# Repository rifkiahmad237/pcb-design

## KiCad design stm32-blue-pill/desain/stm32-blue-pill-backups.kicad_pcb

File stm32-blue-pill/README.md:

# Dokumentasi Desain PCB STM32F103C8T6

## 1. Kapasitor Decoupling

### **Mengapa Diperlukan?**
- Menstabilkan tegangan suplai (**VDD**) agar tidak berfluktuasi akibat switching internal IC.
- Mengurangi noise frekuensi tinggi yang dapat mengganggu operasi mikrokontroler.
- Menyediakan arus instan saat mikrokontroler mengalami perubahan keadaan logika secara cepat.

### **Penempatan Kapasitor Decoupling**
- Harus **sedekat mungkin** dengan pin daya IC untuk mengurangi efek induktansi jalur PCB.
- Nilai umum yang digunakan:
  - **100nF (0.1µF)** untuk setiap pin **VDD**.
  - **4.7µF – 10µF** elektrolit/tantalum untuk stabilisasi tambahan.
  - Untuk filter noise frekuensi tinggi, bisa ditambahkan **1nF**.

---

## 2. Perbedaan Rangkaian Filter VDD dan VDDA

| Tegangan | Fungsi | Rangkaian Filter |
|----------|--------|-----------------|
| **VDD** | Daya utama inti mikrokontroler dan periferal digital. | Kapasitor **100nF + 4.7µF** untuk stabilisasi tegangan. |
| **VDDA** | Daya untuk bagian analog (ADC, DAC). | Filter **RC atau LC** untuk meredam noise dari VDD. |

- **VDDA lebih sensitif terhadap noise**, sehingga perlu pemfilteran tambahan menggunakan ferrite bead atau resistor.

---

## 3. Filter Ferrite Bead untuk VDDA

### **Mengapa Perlu Filter?**
- Noise dari **switching digital** di VDD bisa mempengaruhi ADC jika langsung masuk ke VDDA.
- Ferrite bead berfungsi sebagai **low-pass filter**, menghilangkan noise frekuensi tinggi.
- Rekomendasi umum:
  - **Ferrite bead 600Ω @ 100MHz** (contoh: Murata BLM18AG601SN1D).
  - **Kapasitor 100nF + 1µF** setelah ferrite bead.

### **Alternatif: Filter RC**
- Jika ferrite bead tidak tersedia, bisa menggunakan **resistor 10Ω + kapasitor 1µF** sebagai pengganti.
- Namun, penggunaan resistor bisa menyebabkan sedikit **drop tegangan pada VDDA**.

---

## 4. Sumber Noise Frekuensi Tinggi

| Sumber Noise | Penyebab | Efek pada PCB |
|-------------|---------|--------------|
| **Switching internal mikrokontroler** | Perubahan logika cepat dalam CPU & GPIO | Lonjakan arus sesaat, fluktuasi tegangan pada VDD. |
| **Regulator Switching (DC-DC Converter)** | Frekuensi switching tinggi (150kHz–1MHz) | Ripple tegangan yang bisa masuk ke VDD/VDDA. |
| **Clock dan Kristal Osilator** | Sinyal clock eksternal (8MHz, 16MHz, dll.) | Noise EMI pada jalur PCB. |
| **Desain PCB yang buruk** | Jalur suplai daya terlalu panjang, ground plane tidak optimal | Ground bounce, crosstalk antar sinyal. |
| **Periferal eksternal (motor, relay, LCD)** | Arus transien tinggi | Gangguan pada ADC, kemungkinan reset mendadak. |

### **Solusi untuk Mengurangi Noise:**
- **Gunakan kapasitor decoupling dengan benar**.
- **Gunakan ferrite bead pada VDDA untuk menghilangkan noise dari VDD**.
- **Pastikan tata letak PCB optimal dengan ground plane yang baik**.
- **Pisahkan jalur daya analog dan digital** jika memungkinkan.

---

## 5. VDDA dan VDD: Mengapa Filter Tetap Menghubungkan Ke 3.3V?

- **VDDA** dan **VDD** menggunakan sumber **3.3V yang sama**, namun **VDDA lebih sensitif terhadap noise** dari bagian digital (VDD).
- **Low-pass filter** menggunakan **ferrite bead** dan **kapasitor** bertujuan untuk **mengurangi noise frekuensi tinggi** pada **VDDA** tanpa memisahkan sumber daya sepenuhnya.
- Memisahkan sumber daya untuk VDDA dan VDD bisa dilakukan dengan menggunakan **regulator terpisah**, namun umumnya cukup dengan menggunakan filter untuk penyaringan noise.

---

## 6. Perhitungan Kapasitor untuk Crystal Oscillator (16 MHz)

### **Langkah-langkah Menghitung Kapasitor**

1. **Tentukan Nilai Kapasitansi Seri dan Parasitik dari Kristal**
   - Nilai **C_L** untuk kristal dapat ditemukan di datasheet kristal tersebut (biasanya dalam kisaran 12 pF hingga 30 pF untuk kristal 16 MHz).
   - **Kapasitansi parasitik** PCB biasanya sekitar 2 pF hingga 5 pF.

2. **Rumus Perhitungan Kapasitor Eksternal**
   - Untuk menghitung nilai kapasitor eksternal (C1 dan C2) yang digunakan di sisi kristal, gunakan rumus berikut:
   
   \[
   C_1 = C_2 = 2 \times C_L - C_{parasitik}
   \]

   Di mana:
   - **C_L** adalah kapasitan yang dibutuhkan oleh kristal (misalnya 18 pF),
   - **C_{parasitik}** adalah kapasitansi parasitik (misalnya 5 pF),
   - **C_1** dan **C_2** adalah kapasitor yang dibutuhkan.

### **Contoh Perhitungan**
Misalnya, untuk kristal 16 MHz dengan **C_L = 18 pF** dan **kapasitansi parasitik PCB = 5 pF**:

\[
C_1 = C_2 = 2 \times 18\,\text{pF} - 5\,\text{pF} = 36\,\text{pF} - 5\,\text{pF} = 31\,\text{pF}
\]

Jadi, nilai kapasitor yang digunakan adalah **31 pF** untuk C1 dan C2.

---

## 7. USB (Micro USB) Pinout

Pada desain STM32F103C8T6 yang hanya berfungsi sebagai **peripheral device** (bukan host USB), pin **Shield** dan **Pin ID** dapat **dibiarkan mengambang** atau **floating**.

### **Pin Shield**
- **Fungsi**: Pin ini digunakan untuk **grounding** dan **pelindung** terhadap interferensi elektromagnetik (EMI).
- **Koneksi pada perangkat STM32**: Pin **Shield** dapat **dibiarkan mengambang** atau tidak terhubung langsung ke ground jika perangkat hanya berfungsi sebagai **peripheral device**. Tidak perlu menghubungkannya ke ground.

### **Pin ID**
- **Fungsi**: Pin ini digunakan untuk menentukan apakah perangkat bertindak sebagai **host** atau **peripheral** dalam mode **USB OTG**.
- **Koneksi pada perangkat STM32**: Jika STM32 hanya bertindak sebagai **peripheral device**, pin **ID** dapat **dibiarkan mengambang** atau **floating**. Tidak perlu dihubungkan ke ground karena perangkat tidak akan berfungsi sebagai host USB.

Jadi, pada desain STM32 yang berfungsi sebagai **device-only**, baik pin **Shield** maupun **Pin ID** dapat dibiarkan **floating** tanpa mengganggu fungsionalitas perangkat.

Pada desain USB untuk STM32F103C8T6 yang berfungsi sebagai **peripheral device**, resistor **pull-up 1.5kΩ** perlu ditambahkan pada **pin D+** untuk memungkinkan perangkat dikenali oleh host USB.

### **Fungsi Resistor Pull-up**
- Resistor **1.5kΩ** dihubungkan antara **pin D+** dan **VBUS** (5V) untuk memberi sinyal ke host bahwa perangkat ini adalah **peripheral**.
- Pin **D-** tidak memerlukan resistor pull-up, hanya **D+** yang membutuhkan.
- Dengan resistor ini, perangkat USB dapat berkomunikasi dengan host seperti komputer atau perangkat lainnya.

### **Koneksi**
- **Pin D+** dihubungkan ke **VBUS** melalui resistor **1.5kΩ**.

### **Catatan**
- Penambahan resistor pull-up 1.5kΩ pada pin D+ ini **tidak berlaku untuk semua mikrokontroler STM32**. Namun, pada **STM32F103C8T6**, resistor ini sangat diperlukan agar perangkat dapat dikenali dan berfungsi sebagai peripheral USB.

## 8. Pull-up Resistor pada I2C

Pada komunikasi **I2C**, resistor **pull-up** diperlukan pada jalur **SDA (Serial Data)** dan **SCL (Serial Clock)** karena protokol I2C menggunakan **open-drain**. Tanpa resistor ini, jalur komunikasi bisa **floating**, yang menyebabkan kesalahan dalam transmisi data.

### **Fungsi Pull-up Resistor**
1. **Menjaga Level Logika "High"**  
   - Perangkat I2C hanya dapat menarik jalur ke LOW (GND) tetapi tidak bisa secara aktif mendorongnya ke HIGH.  
   - Resistor pull-up memastikan bahwa saat tidak ada perangkat yang menarik ke LOW, **SDA dan SCL tetap berada di level HIGH**.

2. **Menentukan Kecepatan Transisi Sinyal**  
   - Resistor pull-up mempengaruhi seberapa cepat sinyal berubah dari LOW ke HIGH.
   - Untuk **I2C Fast Mode (400kHz)**, biasanya digunakan **resistor 2.2kΩ** untuk memastikan transisi yang cepat.

3. **Mencegah Floating Signal & Error**  
   - Tanpa pull-up resistor, jalur **SDA** dan **SCL** bisa berada dalam kondisi tidak stabil (floating), menyebabkan komunikasi I2C gagal atau error.

### **Nilai Pull-up Resistor Berdasarkan Kecepatan I2C**
| Kecepatan I2C | Nilai Resistor Pull-up |
|--------------|----------------------|
| **100 kHz (Standard Mode)** | **4.7kΩ – 10kΩ** |
| **400 kHz (Fast Mode)** | **1.8kΩ – 4.7kΩ** (umumnya **2.2kΩ**) |
| **1 MHz (Fast Mode Plus)** | **1kΩ – 2.2kΩ** |
| **3.4 MHz (High-Speed Mode)** | **200Ω – 1kΩ** |

### **Cara Menghubungkan Pull-up Resistor**
- **SDA → Resistor 2.2kΩ → VCC (3.3V atau 5V, sesuai tegangan I2C)**  
- **SCL → Resistor 2.2kΩ → VCC (3.3V atau 5V, sesuai tegangan I2C)**  

*(Pastikan nilai VCC sesuai dengan level tegangan yang digunakan oleh perangkat I2C! Jika STM32 menggunakan 3.3V, maka pull-up harus ke 3.3V.)*

### **Kesimpulan**
- **Pull-up resistor sangat penting dalam komunikasi I2C** untuk menjaga kestabilan sinyal.  
- Nilai **2.2kΩ** digunakan untuk **I2C Fast Mode (400kHz)** agar transisi sinyal cepat dan stabil.  
- Tanpa resistor pull-up, **SDA dan SCL bisa floating**, menyebabkan error atau komunikasi yang tidak berjalan.  

## 9. Pemilihan Footprint Komponen

Memilih footprint yang tepat sangat penting agar komponen dapat dipasang dengan baik dan proses soldering berjalan lancar. Berikut adalah panduan dalam memilih footprint yang sesuai.

### **1. Jenis Footprint Berdasarkan Komponen**
Komponen PCB memiliki dua jenis utama berdasarkan cara pemasangannya:
- **Through-Hole (THT)** → Memiliki lubang pada PCB untuk kaki komponen. Cocok untuk solder manual.
- **Surface Mount Device (SMD)** → Tidak memiliki lubang, hanya pad tembaga. Cocok untuk reflow soldering.

Contoh package dan footprint yang sering digunakan:
| **Komponen** | **Jenis Package** | **Footprint PCB** |
|-------------|-----------------|------------------|
| **STM32F103C8T6** | LQFP-48 | LQFP-48 (7x7mm, 0.5mm pitch) |
| **Resistor SMD** | 0805 | 0805 (2.0mm x 1.25mm) |
| **Kapasitor SMD** | 0603 | 0603 (1.6mm x 0.8mm) |
| **LED SMD** | 1206 | 1206 (3.2mm x 1.6mm) |
| **Konektor USB Micro** | SMD/THT | USB-Micro-B-5P |
| **Crystal 16MHz** | HC-49S | HC-49S (Through-hole) atau SMD-3225 |
| **AMS1117-3.3V** | SOT-223 | SOT-223 (SMD) |

### **2. Faktor yang Harus Diperhatikan dalam Memilih Footprint**
1. **Sesuai dengan Datasheet Komponen**  
   - Periksa dimensi kaki, pitch (jarak antar pin), dan ukuran pad solder.  
2. **Ukuran Pad dan Lubang Solder**  
   - **THT** → Lubang harus sedikit lebih besar dari kaki komponen agar mudah dipasang.  
   - **SMD** → Pad harus cukup besar untuk soldering manual atau reflow.  
3. **Clearance Antar Komponen**  
   - Pastikan ada ruang cukup agar soldering tidak sulit.  
   - Untuk sinyal high-speed, gunakan **clearance minimal 0.2mm – 0.5mm**.  
4. **Metode Soldering**  
   - **Manual** → Gunakan footprint yang lebih besar agar lebih mudah disolder.  
   - **Reflow** → Gunakan footprint standar sesuai datasheet.  
5. **Orientasi & Polaritas Komponen**  
   - Pin 1 pada IC harus sesuai dengan marking di footprint PCB.  
   - LED, kapasitor elektrolit, dan dioda harus memiliki tanda polaritas.  

### **3. Cara Memeriksa Footprint Sebelum Produksi**
- Gunakan **3D Viewer di software PCB** (seperti KiCad atau Altium) untuk mengecek dimensi.  
- Cetak layout PCB dalam skala **1:1**, lalu tempelkan komponen fisik untuk memastikan kecocokan.  
- Periksa **clearance antar komponen** terutama pada area padat seperti konektor dan IC.  
- Pastikan **solder pad cukup besar** agar mudah disolder.  
### **4. Jenis-Jenis Package Komponen dan Penggunaannya**

| **Jenis Package** | **Deskripsi** | **Digunakan untuk** | **Gambar** |
|------------------|--------------|----------------------|------------|
| **SOIC (Small Outline IC)** | IC dengan kaki menonjol keluar di kedua sisi, lebih besar dari TSSOP. | IC dengan jumlah pin sedang, seperti op-amp atau mikrokontroler kecil. | *(Tambahkan gambar di sini)* |
| **TSSOP (Thin Shrink Small Outline Package)** | Versi lebih tipis dan rapat dari SOIC, menghemat ruang PCB. | IC kecil dengan banyak pin seperti regulator atau sensor. | *(Tambahkan gambar di sini)* |
| **QFP (Quad Flat Package)** | IC dengan kaki di keempat sisi, tersedia dalam berbagai ukuran. | STM32F103C8T6 (LQFP-48), mikrokontroler, FPGA. | *(Tambahkan gambar di sini)* |
| **QFN (Quad Flat No-Lead)** | IC tanpa kaki menonjol, hanya pad solder di bawahnya. | IC kecil dengan performa tinggi, konverter daya, sensor digital. | *(Tambahkan gambar di sini)* |
| **BGA (Ball Grid Array)** | IC dengan bola solder di bawahnya, membutuhkan reflow soldering. | Prosesor, memori flash, IC berkecepatan tinggi. | *(Tambahkan gambar di sini)* |
| **0805 (SMD Resistor/Kapasitor)** | 2.0mm x 1.25mm, mudah disolder secara manual. | Resistor dan kapasitor SMD umum. | *(Tambahkan gambar di sini)* |
| **0603 (SMD Resistor/Kapasitor)** | 1.6mm x 0.8mm, lebih kecil dari 0805. | Resistor dan kapasitor untuk desain yang lebih ringkas. | *(Tambahkan gambar di sini)* |
| **0402 (SMD Resistor/Kapasitor)** | 1.0mm x 0.5mm, sulit disolder manual. | Desain berukuran kecil dengan kepadatan tinggi. | *(Tambahkan gambar di sini)* |

💡 **Catatan**:  
- **QFP lebih mudah disolder manual dibanding QFN dan BGA** karena memiliki kaki yang terlihat.  
- **QFN dan BGA membutuhkan soldering reflow dan sulit diperbaiki secara manual**.  
- **Komponen ukuran 0805 lebih mudah disolder dibanding 0603 atau 0402**, sehingga lebih cocok untuk pemula.  

🔹 Untuk menambahkan gambar, bisa menggunakan format markdown berikut setelah mengunggah gambarnya:  
### **Kesimpulan**
- Gunakan **footprint yang sesuai datasheet** untuk menghindari kesalahan produksi.  
- Perhatikan **ukuran pad, lubang solder, dan clearance** agar proses soldering lebih mudah.  
- Lakukan pengecekan dengan **3D viewer atau cetak layout skala 1:1** sebelum memesan PCB.  
- Pastikan **IC, konektor, dan komponen dengan polaritas** memiliki marking yang jelas agar tidak salah pasang.  

# Faktor yang Mempengaruhi Kualitas Jalur pada PCB  

Desain jalur pada PCB sangat berpengaruh terhadap kualitas sinyal, terutama pada sinyal frekuensi tinggi. Berikut adalah faktor-faktor utama yang mempengaruhi kualitas jalur:  

## 1. Impedansi Jalur  

### **Apa itu Impedansi?**  
Impedansi (\(Z\)) adalah hambatan total dalam jalur PCB yang terdiri dari resistansi, induktansi, dan kapasitansi. Nilai impedansi sangat penting dalam desain **high-speed signal** dan **differential pairs**.  

### **Faktor yang Mempengaruhi Impedansi:**  
| Faktor | Pengaruh terhadap Impedansi |
|--------|-----------------------------|
| **Lebar jalur** | Jalur lebih lebar → Impedansi lebih rendah |
| **Jarak ke ground plane** | Jarak lebih dekat → Impedansi lebih rendah |
| **Konstanta dielektrik PCB (\( \varepsilon_r \))** | \( \varepsilon_r \) lebih tinggi → Impedansi lebih rendah |
| **Ketebalan tembaga** | Tembaga lebih tebal → Impedansi lebih rendah |
| **Jarak antar pasangan diferensial** | Jarak lebih dekat → Impedansi lebih rendah |

### **Dampak jika impedansi tidak sesuai:**  
- **Refleksi sinyal**, yang menyebabkan distorsi data.  
- **Penurunan kecepatan komunikasi** akibat sinyal yang tidak terdeteksi dengan baik.  
- **Ketidaksesuaian dengan standar (USB, HDMI, PCIe, dll.)**.  

---

## 2. Induktansi Jalur  

### **Apa itu Induktansi?**  
Induktansi adalah kemampuan jalur PCB untuk menyimpan energi dalam bentuk medan magnet ketika arus melewatinya.  

### **Faktor yang Meningkatkan Induktansi:**  
| Faktor | Pengaruh terhadap Induktansi |
|--------|-----------------------------|
| **Jalur lebih panjang** | Induktansi lebih tinggi |
| **Jalur lebih sempit** | Induktansi lebih tinggi |
| **Jarak lebih jauh dari ground plane** | Induktansi lebih tinggi |
| **Tidak adanya ground return path yang dekat** | Induktansi lebih tinggi |

### **Dampak Induktansi Tinggi:**  
- **Menurunkan integritas sinyal** akibat distorsi dan ringing.  
- **Menyebabkan overshoot dan undershoot pada sinyal digital**.  
- **Menimbulkan EMI (Electromagnetic Interference) yang lebih besar**.  

✅ **Solusi:**  
- Gunakan **ground plane** yang dekat dengan jalur.  
- Jaga agar jalur tetap **pendek dan lebar**.  
- Untuk sinyal high-speed, gunakan **jalur diferensial** untuk mengurangi EMI.  

---

## 3. Kapasitansi Jalur  

### **Apa itu Kapasitansi?**  
Kapasitansi adalah kemampuan jalur untuk menyimpan muatan listrik dalam medan listrik antara jalur dan ground plane.  

### **Faktor yang Meningkatkan Kapasitansi:**  
| Faktor | Pengaruh terhadap Kapasitansi |
|--------|-----------------------------|
| **Jarak kecil antara jalur dan ground plane** | Kapasitansi lebih besar |
| **Jalur lebih lebar di dekat ground plane** | Kapasitansi lebih besar |
| **Material PCB dengan konstanta dielektrik tinggi (\( \varepsilon_r \))** | Kapasitansi lebih besar |

### **Dampak Kapasitansi Tinggi:**  
- **Sinyal menjadi lebih lambat** karena waktu propagasi meningkat.  
- **Pelemahan sinyal (signal attenuation)**, terutama pada frekuensi tinggi.  
- **Cross-talk antar jalur meningkat**, menyebabkan interferensi antar sinyal.  

✅ **Solusi:**  
- Jaga jarak antara jalur dan ground plane sesuai perhitungan impedansi.  
- Gunakan **material dengan konstanta dielektrik rendah** untuk mengurangi efek kapasitif.  
- Gunakan jalur **lebih sempit** untuk mengurangi luas permukaan yang bersentuhan dengan ground plane.  

---

## 4. Resistansi Jalur  

### **Apa itu Resistansi?**  
Resistansi adalah hambatan listrik yang terjadi akibat sifat material tembaga dan panjang jalur pada PCB.  

### **Faktor yang Meningkatkan Resistansi:**  
| Faktor | Pengaruh terhadap Resistansi |
|--------|-----------------------------|
| **Jalur lebih panjang** | Resistansi lebih tinggi |
| **Jalur lebih sempit** | Resistansi lebih tinggi |
| **Ketebalan tembaga lebih tipis** | Resistansi lebih tinggi |

### **Dampak Resistansi Tinggi:**  
- **Tegangan drop lebih besar**, terutama pada jalur daya.  
- **Panas berlebih pada PCB**, yang dapat menyebabkan degradasi komponen.  
- **Penurunan performa sinyal**, terutama pada frekuensi tinggi.  

✅ **Solusi:**  
- Gunakan **jalur lebih lebar** untuk daya tinggi.  
- Gunakan **tembaga lebih tebal** (misalnya 2 oz/ft² dibandingkan 1 oz/ft²).  
- Minimalkan panjang jalur untuk mengurangi resistansi total.  

---

## 5. Kesimpulan  

Untuk mendesain PCB dengan kualitas sinyal yang baik, pertimbangkan faktor-faktor berikut:  

| Faktor | Efek Positif | Efek Negatif |
|--------|-------------|-------------|
| **Impedansi yang sesuai** | Mengurangi refleksi, kompatibel dengan standar komunikasi | Jika salah, sinyal bisa terdistorsi |
| **Induktansi rendah** | Mengurangi EMI dan ringing | Jika tinggi, menyebabkan gangguan sinyal |
| **Kapasitansi terkontrol** | Mempertahankan kecepatan sinyal | Jika tinggi, bisa memperlambat sinyal dan menyebabkan cross-talk |
| **Resistansi rendah** | Mengurangi panas dan tegangan drop | Jika tinggi, menyebabkan penurunan performa dan overheat |

**Rekomendasi umum untuk jalur PCB:**  
- Gunakan **impedansi terkendali** untuk sinyal high-speed.  
- Pastikan **ground plane selalu dekat dengan jalur** untuk mengurangi EMI dan meningkatkan return path.  
- Gunakan **jalur lebar untuk daya**, dan **jalur sempit dengan perhitungan yang sesuai untuk sinyal high-speed**.  
- Pilih material PCB yang sesuai untuk kebutuhan desain (misalnya FR4 atau Rogers untuk RF).  

Dengan memahami konsep ini, desain PCB akan lebih optimal dalam performa, daya tahan, dan kualitas sinyal. 🚀  

# Differential Pair pada Desain PCB (USB)

Pada desain PCB dengan sinyal **differential pair** seperti USB, penting untuk mengatur beberapa parameter untuk menjaga kualitas sinyal dan memastikan impedansi sesuai standar.

## 1. **Width (Lebar Jalur)**
- **Width** adalah lebar dari jalur **differential pair** (misalnya D+ dan D- untuk USB).
- Lebar jalur berpengaruh pada **impedansi** sinyal.
- Untuk USB, impedansi yang diinginkan adalah sekitar **90Ω**.
- Lebar jalur yang lebih lebar akan menghasilkan **impedansi lebih rendah**, sementara jalur yang lebih sempit menghasilkan **impedansi lebih tinggi**.
- Lebar jalur harus disesuaikan dengan **ketebalan tembaga** pada PCB dan **konstanta dielektrik** bahan PCB.

## 2. **Gap (Jarak Antar Jalur)**
- **Gap** adalah jarak antara dua jalur yang membentuk differential pair (D+ dan D-).
- Jarak yang tepat antara jalur ini penting untuk menjaga **impedansi**.
- Jika gap terlalu kecil, impedansi bisa terlalu rendah, menyebabkan **refleksi** dan **distorsi sinyal**.
- Jika gap terlalu besar, impedansi bisa terlalu tinggi, mempengaruhi kualitas sinyal.
- Pada USB, gap umumnya sekitar **0.2 mm – 0.25 mm**, tergantung pada lebar jalur dan bahan PCB.

## 3. **Via Gap (Jarak Via)**
- **Via gap** adalah jarak antara **via** yang digunakan untuk menghubungkan jalur pada layer yang berbeda.
- **Via gap** yang tepat memastikan integritas sinyal dan menghindari masalah **refleksi**.
- Penggunaan **via** dalam jalur differential pair sebaiknya diminimalisir untuk menjaga kualitas sinyal.
- Jika menggunakan via, pastikan jarak dan ukurannya sesuai dengan standar desain impedansi.

## Mengapa Hal Ini Penting?
- **Integritas sinyal** sangat penting pada desain dengan sinyal kecepatan tinggi seperti USB.
- Mengatur **width**, **gap**, dan **via gap** dengan benar membantu menjaga kualitas sinyal dan memastikan transmisi data yang stabil.
- Tanpa pengaturan yang tepat, dapat muncul masalah seperti **data corruption**, **distorsi sinyal**, atau **komunikasi USB yang tidak stabil**.

---

<!-- ## 7. Kesimpulan
- Kapasitor decoupling wajib digunakan untuk menstabilkan VDD dan mengurangi noise.
- VDDA membutuhkan filter tambahan (**RC atau LC**) untuk memastikan tegangan analog bersih.
- Noise frekuensi tinggi bisa berasal dari switching internal, clock, switching regulator, atau layout PCB yang buruk.
- Ferrite bead lebih efektif dibanding resistor dalam menyaring noise tanpa menyebabkan drop tegangan signifikan.
- **VDDA tetap terhubung dengan 3.3V yang sama dengan VDD**, namun menggunakan filter untuk mengurangi noise dari VDD.
- Untuk kristal 16 MHz, kapasitor C1 dan C2 biasanya dihitung sebagai **31 pF** jika kapasitansi parasitik sekitar 5 pF. -->

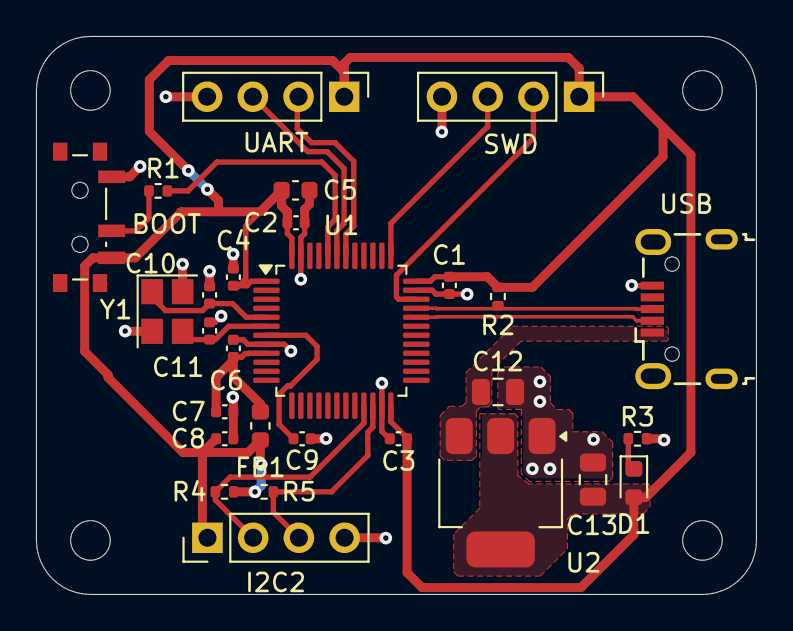
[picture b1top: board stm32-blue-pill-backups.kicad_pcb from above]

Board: 2 copper layers, 40.0 x 31.0 mm, 32 parts (0 on the bottom side), 18 nets.

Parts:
BOOT: SW_SPDT; SW_SPDT_PCM12
C1, C2, C3, C4, C9: 100n; C_0402_1005Metric
C5: 10u; C_0603_1608Metric
C6: 10n; C_0402_1005Metric
C7, C8: 1u; C_0402_1005Metric
C10, C11: 10p; C_0402_1005Metric
C12, C13: 22u; C_0805_2012Metric
D1: LED_RED; LED_0603_1608Metric
FB1: 120R; L_0603_1608Metric
H1, H2, H3, H4: MountingHole; MountingHole_2.2mm_M2
I2C2: Conn_01x04_Pin; PinHeader_1x04_P2.54mm_Vertical
R1: 10k; R_0402_1005Metric
R2, R3, R4, R5: 1k5; R_0402_1005Metric
SWD: Conn_01x04_Pin; PinHeader_1x04_P2.54mm_Vertical
U1: STM32F103C8Tx; LQFP-48_7x7mm_P0.5mm
U2: AMS1117-3.3; SOT-223-3_TabPin2
UART: Conn_01x04_Pin; PinHeader_1x04_P2.54mm_Vertical
USB: USB_B_Micro; USB_Micro-B_Wuerth_629105150521
Y1: 16Mhz; Crystal_SMD_3225-4Pin_3.2x2.5mm

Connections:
+3.3V: BOOT.3 (C), C1.1, C2.1, C3.1, C4.1, C5.1, C8.1, C13.1, D1.2 (A), FB1.1, I2C2.1, R2.2, R4.1, R5.1, SWD.1, U1.1 (VBAT), U1.24 (VDD), U1.36 (VDD), U1.48 (VDD), U2.2 (VO), UART.1
+3.3VA: C6.1, C7.1, FB1.2, U1.9 (VDDA)
/BOOT0: R1.2, U1.44 (BOOT0)
/HSI_IN: C10.1, U1.5 (PD0), Y1.1
/HSI_OUT: C11.1, U1.6 (PD1), Y1.3
/I2C2_SCL: I2C2.2, R4.2, U1.21 (PB10)
/I2C2_SDA: I2C2.3, R5.2, U1.22 (PB11)
/NRST: C9.1, U1.7 (NRST)
/SWCLK: SWD.3, U1.37 (PA14)
/SWDIO: SWD.2, U1.34 (PA13)
/SW_BOOT0: BOOT.2 (B), R1.1
/USART1_RX: U1.43 (PB7), UART.3
/USART1_TX: U1.42 (PB6), UART.2
/USB_D+: R2.1, U1.33 (PA12), USB.3 (D+)
/USB_D-: U1.32 (PA11), USB.2 (D-)
GND: BOOT.1 (A), C1.2, C2.2, C3.2, C4.2, C5.2, C6.2, C7.2, C8.2, C9.2, C10.2, C11.2, C12.2, C13.2, I2C2.4, R3.2, SWD.4, U1.8 (VSSA), U1.23 (VSS), U1.35 (VSS), U1.47 (VSS), U2.1 (GND), UART.4, USB.5 (GND), Y1.2, Y1.4
unnamed: D1.1 (K), R3.1
VBUS: C12.1, U2.3 (VI), USB.1 (VBUS)

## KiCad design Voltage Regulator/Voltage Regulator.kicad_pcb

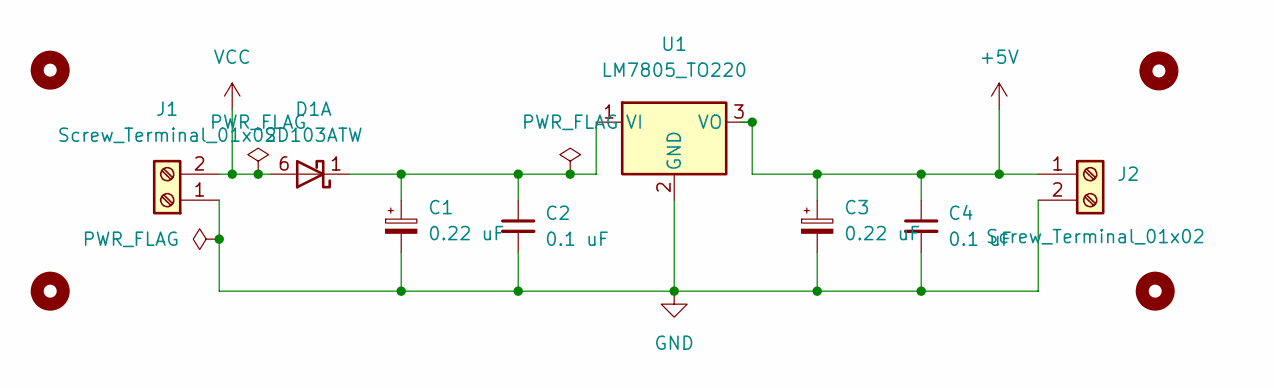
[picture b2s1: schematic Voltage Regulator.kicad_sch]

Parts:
C1: 0.22 uF; CP_Radial_D5.0mm_P2.50mm
C2, C4: 0.1 uF; CP_Radial_D4.0mm_P1.50mm
C3: 0.22 uF; CP_Radial_D5.0mm_P2.00mm
D1: SD103ATW; SOT-363_SC-70-6
H1, H2, H3, H4: MountingHole; MountingHole_2.2mm_M2_ISO14580_Pad
J1, J2: Screw_Terminal_01x02; TerminalBlock_Phoenix_MKDS-1,5-2-5.08_1x02_P5.08mm_Horizont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
U1: LM7805_TO220; TO-220-3_Vertical

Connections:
+5V: C3.1, C4.1, J2.1, U1.3 (VO)
GND: C1.2, C2.2, C3.2, C4.2, J1.1, J2.2, U1.2 (GND)
unnamed: C1.1, C2.1, D1.1 (K), U1.1 (VI)
VCC: D1.6 (A), J1.2

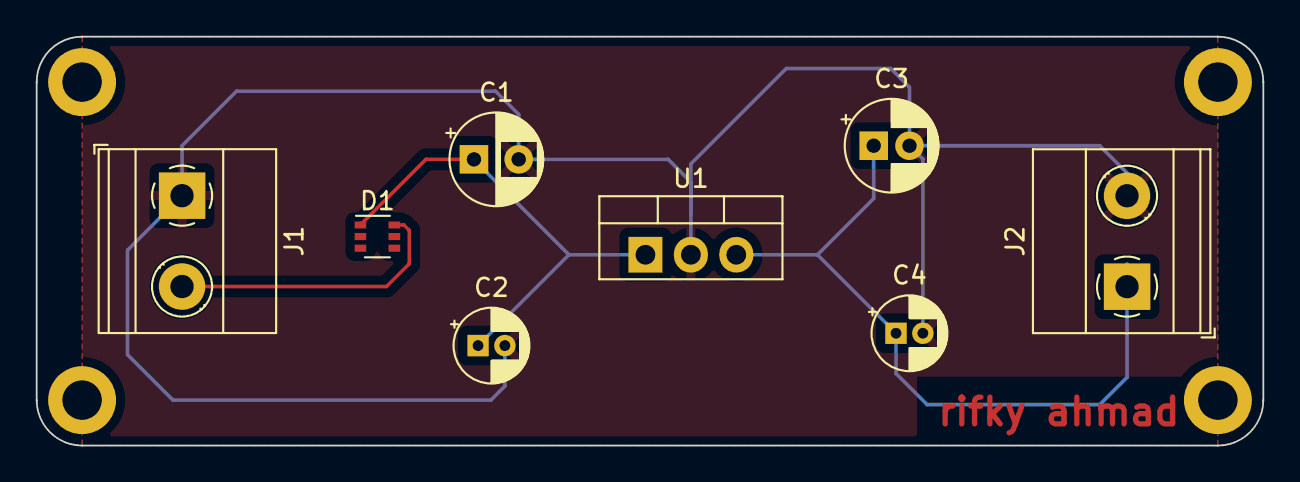
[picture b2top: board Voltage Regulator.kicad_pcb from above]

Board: 2 copper layers, 68.6 x 22.9 mm, 12 parts (0 on the bottom side), 4 nets.

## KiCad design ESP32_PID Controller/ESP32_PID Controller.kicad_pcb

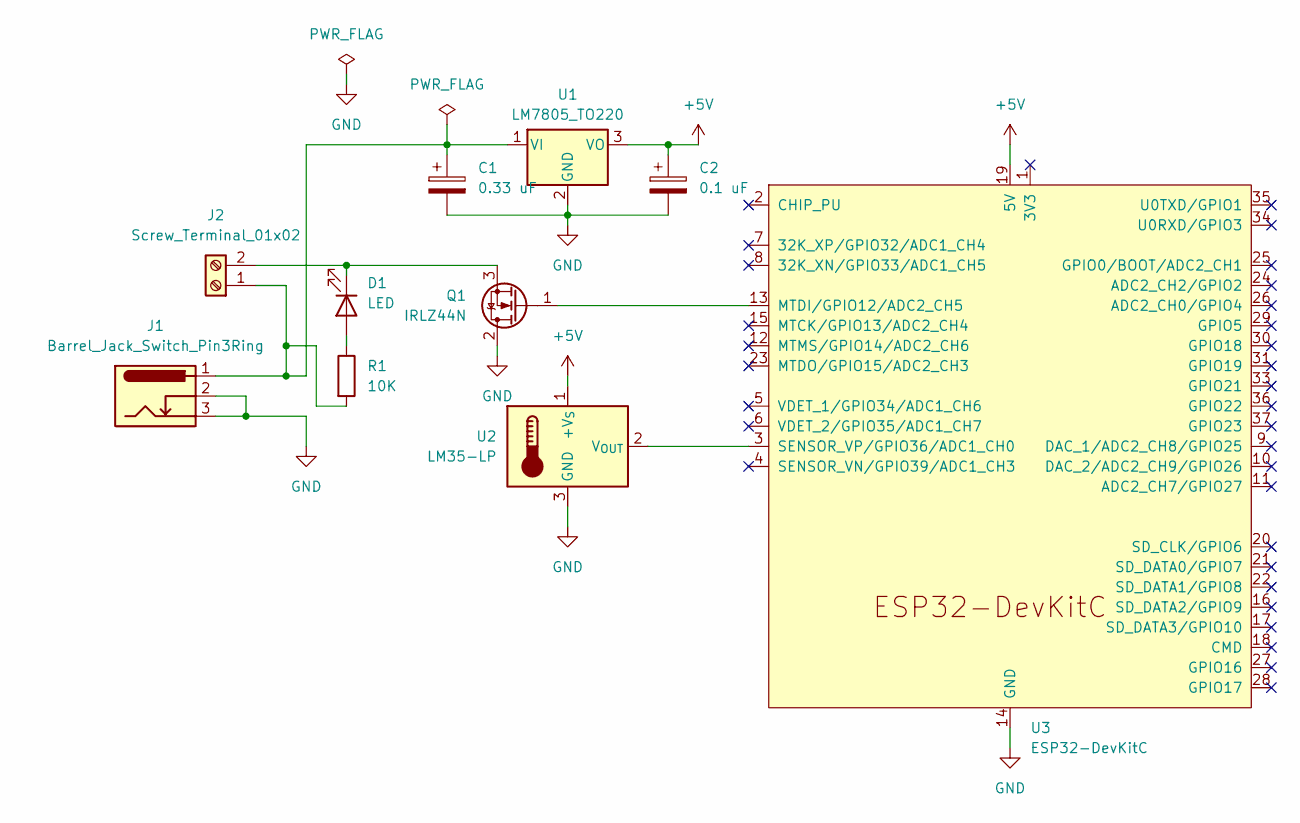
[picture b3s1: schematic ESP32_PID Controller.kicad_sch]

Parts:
C1: 0.33 uF; CP_Radial_D5.0mm_P2.50mm
C2: 0.1 uF; CP_Radial_D5.0mm_P2.50mm
D1: LED; LED_D3.0mm
J1: Barrel_Jack_Switch_Pin3Ring; BarrelJack_Horizontal
J2: Screw_Terminal_01x02; TerminalBlock_Phoenix_MKDS-1,5-2_1x02_P5.00mm_Horizontal
Q1: IRLZ44N; TO-220-3_Vertical
R1: 10K; R_Axial_DIN0414_L11.9mm_D4.5mm_P15.24mm_Horizontal
U1: LM7805_TO220; TO-220-3_Vertical
U2: LM35-LP; TO-92_Inline
U3: ESP32-DevKitC

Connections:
+5V: C2.1, U1.3 (VO), U2.1 (+V_{S}), U3.19 (5V)
GND: C1.2, C2.2, J1.2, J1.3, Q1.2 (D), U1.2 (GND), U2.3 (GND), U3.14 (GND), U3.32 (GND), U3.38 (GND)
unnamed: D1.2 (A), R1.1
unnamed: D1.1 (K), J2.2, Q1.3 (S)
unnamed: C1.1, J1.1, J2.1, R1.2, U1.1 (VI)
unnamed: Q1.1 (G), U3.13 (MTDI/GPIO12/ADC2_CH5)
unnamed: U2.2 (V_{OUT}), U3.3 (SENSOR_VP/GPIO36/ADC1_CH0)

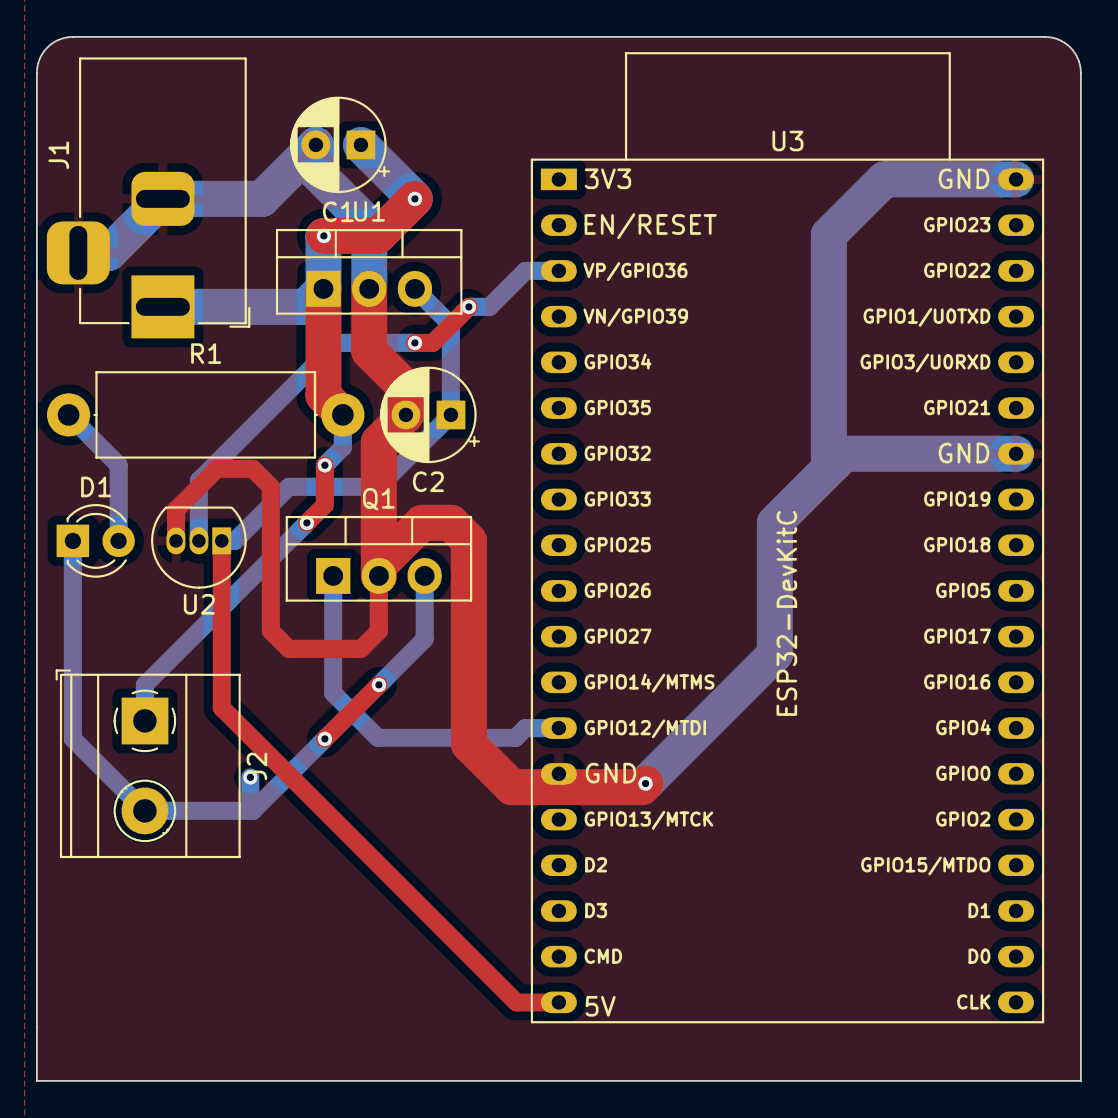
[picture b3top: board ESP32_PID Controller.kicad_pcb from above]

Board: 2 copper layers, 58.0 x 58.0 mm, 10 parts (0 on the bottom side), 7 nets.

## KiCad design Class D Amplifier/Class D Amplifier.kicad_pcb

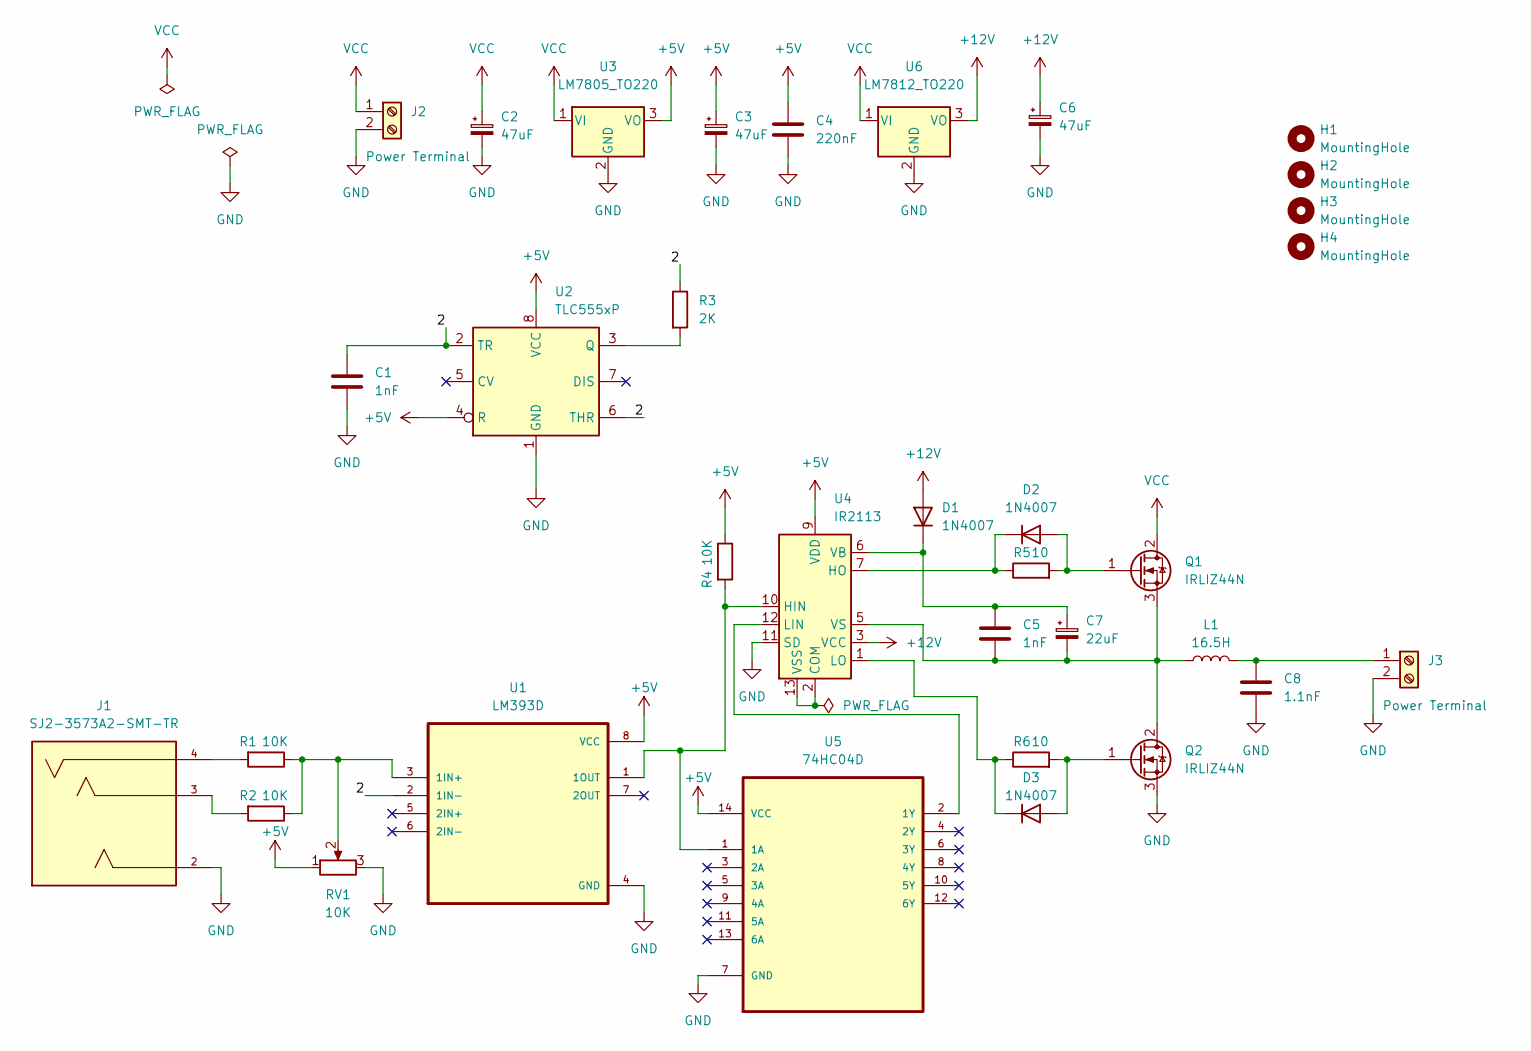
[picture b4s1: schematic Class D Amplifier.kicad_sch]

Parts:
C1, C5: 1nF; CP_Radial_D5.0mm_P2.50mm
C2, C3, C6: 47uF; CP_Radial_D5.0mm_P2.50mm
C4: 220nF; CP_Radial_D5.0mm_P2.50mm
C7: 22uF; CP_Radial_D5.0mm_P2.50mm
C8: 1.1nF; CP_Radial_D5.0mm_P2.50mm
D1, D2, D3: 1N4007; D_DO-41_SOD81_P10.16mm_Horizontal
H1, H2, H3, H4: MountingHole; MountingHole_2.7mm_M2.5_ISO7380_Pad_TopBottom
J1: SJ2-3573A2-SMT-TR; CUI_SJ2-3573A2-SMT-TR; MPN SJ2-3573A2-SMT-TR
J2, J3: Power Terminal; TerminalBlock_Phoenix_MKDS-1,5-2-5.08_1x02_P5.08mm_Horizont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
L1: 16.5H; L_Radial_D6.0mm_P4.00mm
Q1, Q2: IRLIZ44N; TO-220F-3_Vertical
R1, R2, R4: 10K; R_Axial_DIN0207_L6.3mm_D2.5mm_P10.16mm_Horizontal
R3: 2K; R_Axial_DIN0207_L6.3mm_D2.5mm_P10.16mm_Horizontal
R5, R6: 10; R_Axial_DIN0207_L6.3mm_D2.5mm_P10.16mm_Horizontal
RV1: 10K; Potentiometer_Bourns_3386C_Horizontal
U1: LM393D; SOIC127P599X175-8N
U2: TLC555xP; DIP-8_W7.62mm
U3: LM7805_TO220; TO-220-3_Vertical
U4: IR2113; DIP-14_W7.62mm
U5: 74HC04D; SOIC127P600X175-14N; MPN 74HC04D
U6: LM7812_TO220; TO-220-3_Vertical

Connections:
+5V: C3.1, C4.1, R4.1, RV1.1, U1.8 (VCC), U2.4 (R), U2.8 (VCC), U3.3 (VO), U4.9 (VDD), U5.14 (VCC)
+12V: C6.1, D1.2 (A), U4.3 (VCC), U6.3 (VO)
/2: C1.1, R3.1, U1.2 (1IN-), U2.2 (TR), U2.6 (THR)
GND: C1.2, C2.2, C3.2, C4.2, C6.2, C8.2, J1.2, J2.2, J3.2, Q2.3 (S), RV1.3, U1.4 (GND), U2.1 (GND), U3.2 (GND), U4.11 (SD), U5.7 (GND), U6.2 (GND)
unnamed: C5.1, C7.1, D1.1 (K), U4.6 (VB)
unnamed: D2.2 (A), Q1.1 (G), R5.2
unnamed: D2.1 (K), R5.1, U4.7 (HO)
unnamed: D3.2 (A), Q2.1 (G), R6.2
unnamed: D3.1 (K), R6.1, U4.1 (LO)
unnamed: J1.3, R2.2
unnamed: J1.4, R1.2
unnamed: C8.1, J3.1, L1.2
unnamed: C5.2, C7.2, L1.1, Q1.3 (S), Q2.2 (D), U4.5 (VS)
unnamed: R1.1, R2.1, RV1.2, U1.3 (1IN+)
unnamed: R4.2, U1.1 (1OUT), U4.10 (HIN), U5.1 (1A)
unnamed: R3.2, U2.3 (Q)
unnamed: U4.2 (COM), U4.13 (VSS)
unnamed: U4.12 (LIN), U5.2 (1Y)
VCC: C2.1, J2.1, Q1.2 (D), U3.1 (VI), U6.1 (VI)

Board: 2 copper layers, 34 parts (0 on the bottom side), 19 nets, no tracks yet.

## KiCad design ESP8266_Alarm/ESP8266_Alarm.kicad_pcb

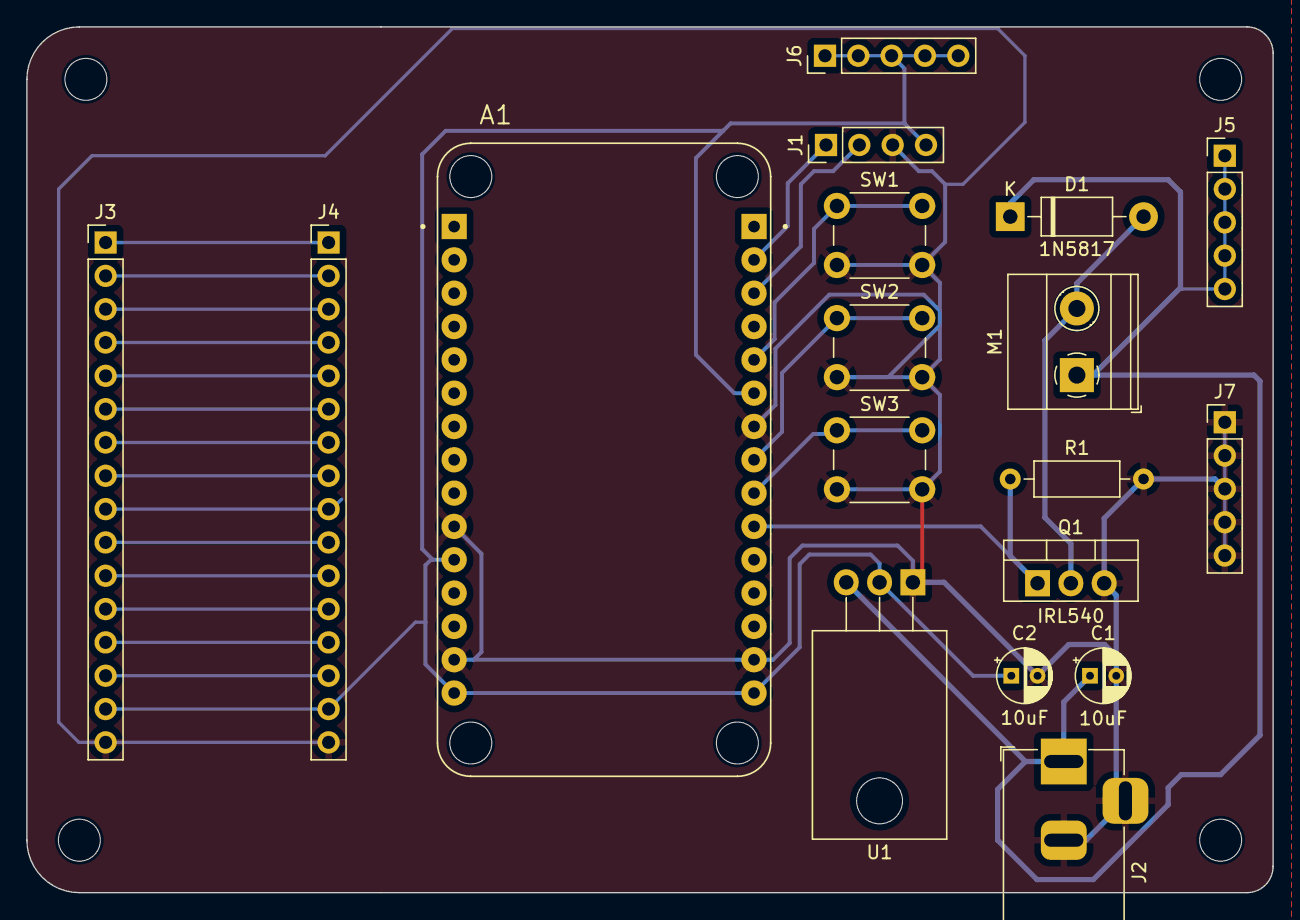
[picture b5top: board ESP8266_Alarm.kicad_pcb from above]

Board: 2 copper layers, 95.0 x 66.0 mm, 22 parts (0 on the bottom side), 24 nets.

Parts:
A1: Nodemcu V2_ESP8266
C1, C2: 10uF; CP_Radial_D4.0mm_P2.00mm
D1: 1N5817; D_DO-41_SOD81_P10.16mm_Horizontal
H1, H2, H3, H4: MountingHole; MountingHole_3.2mm_M3
J1: Conn_01x04_Pin; PinHeader_1x04_P2.54mm_Vertical
J2: Barrel_Jack_Switch; BarrelJack_Horizontal
J3, J4: Conn_01x16_Pin; PinHeader_1x16_P2.54mm_Vertical
J5, J6, J7: Conn_01x05_Pin; PinHeader_1x05_P2.54mm_Vertical
M1: Motor_DC; TerminalBlock_Phoenix_MKDS-1,5-2-5.08_1x02_P5.08mm_Horizont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
Q1: IRL540; TO-220-3_Vertical
R1: 10K; R_Axial_DIN0207_L6.3mm_D2.5mm_P10.16mm_Horizontal
SW1, SW2, SW3: SW_Push; SW_PUSH_6mm_H4.3mm
U1: LM1117T-3.3; TO-220-3_Horizontal_TabDown

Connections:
+3.3V: A1.J1_11 (3V3), A1.J1_15 (VIN), A1.J2_6 (3V3), A1.J2_15 (3V3), C2.1, J1.4, J3.15, J4.15, J6.1, J6.2, J6.3, J6.4, J6.5, U1.2 (VO)
+12V: C1.1, D1.1 (K), J2.1, J5.1, J5.2, J5.3, J5.4, J5.5, M1.1 (+), U1.3 (VI)
/D1: A1.J2_2 (D1), J1.1
/D2: A1.J2_3 (D2), J1.2
/D4: A1.J2_5 (D4), SW1.1
/D5: A1.J2_8 (D5), SW2.1
/D6: A1.J2_9 (D6), SW3.1
/D7: A1.J2_10 (D7), Q1.1 (G), R1.1
GND: A1.J1_10 (GND), A1.J1_14 (GND), A1.J2_7 (GND), A1.J2_14 (GND), C1.2, C2.2, J1.3, J2.2, J2.3, J3.16, J4.16, J7.1, J7.2, J7.3, J7.4, J7.5, Q1.3 (S), R1.2, SW1.2, SW2.2, SW3.2, U1.1 (GND)
unnamed: D1.2 (A), M1.2 (-), Q1.2 (D)
unnamed: J3.1, J4.1
unnamed: J3.2, J4.2
unnamed: J3.3, J4.3
unnamed: J3.4, J4.4
unnamed: J3.5, J4.5
unnamed: J3.6, J4.6
unnamed: J3.7, J4.7
unnamed: J3.8, J4.8
unnamed: J3.9, J4.9
unnamed: J3.10, J4.10
unnamed: J3.11, J4.11
unnamed: J3.12, J4.12
unnamed: J3.13, J4.13
unnamed: J3.14, J4.14

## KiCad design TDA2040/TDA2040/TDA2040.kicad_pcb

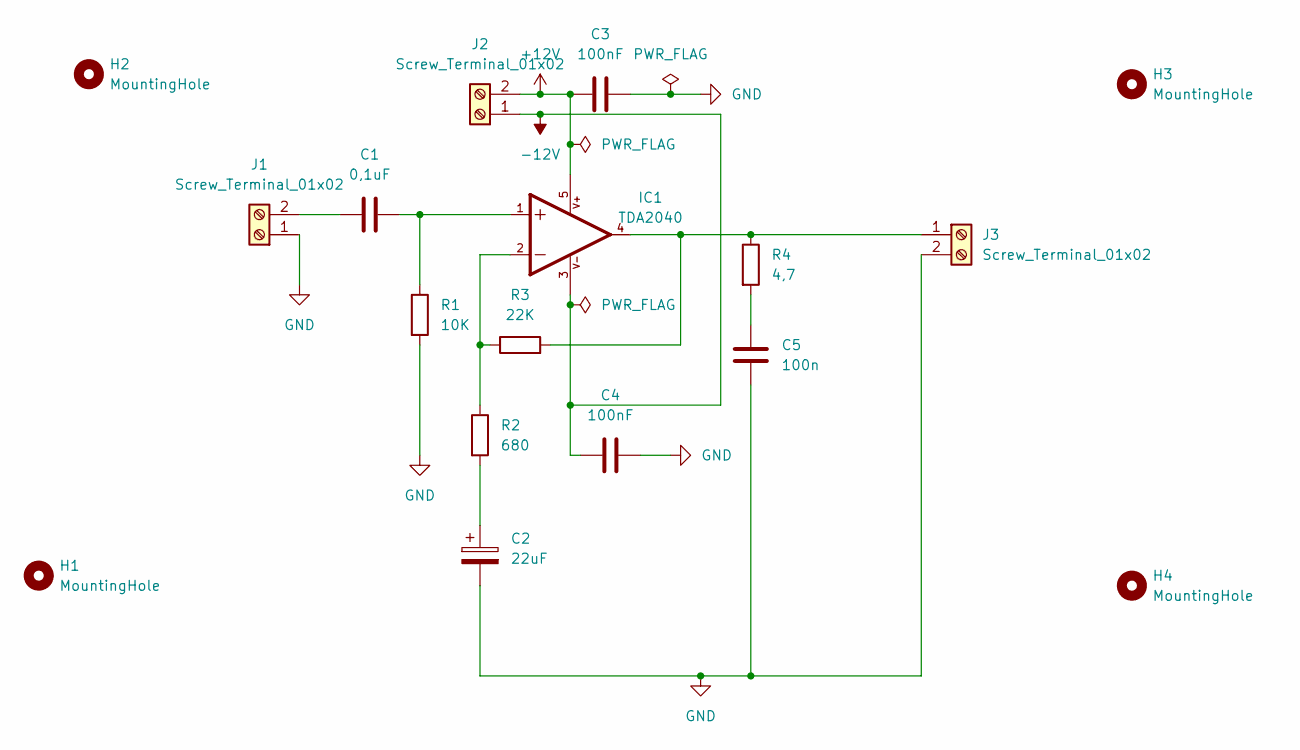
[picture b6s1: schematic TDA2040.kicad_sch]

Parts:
C1: 0,1uF; C_0402_1005Metric
C2: 22uF; CP_Elec_3x5.3
C3, C4: 100nF; C_0201_0603Metric
C5: 100n; C_0201_0603Metric
H1, H2, H3, H4: MountingHole; MountingHole_2.2mm_M2_DIN965_Pad
IC1: TDA2040; CB360
J1, J2, J3: Screw_Terminal_01x02; TerminalBlock_Phoenix_MKDS-1,5-2-5.08_1x02_P5.08mm_Horizont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
R1: 10K; R_0402_1005Metric
R2: 680; R_0201_0603Metric_Pad0.64x0.40mm_HandSolder
R3: 22K; R_0201_0603Metric
R4: 4,7; R_0201_0603Metric_Pad0.64x0.40mm_HandSolder

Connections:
+12V: C3.2, IC1.5, J2.2
-12V: C4.2, IC1.3, J2.1
GND: C2.2, C3.1, C4.1, C5.2, J1.1, J3.2, R1.2
unnamed: C2.1, R2.2
unnamed: C5.1, R4.2
unnamed: C1.1, IC1.1, R1.1
unnamed: IC1.2, R2.1, R3.1
unnamed: IC1.4, J3.1, R3.2, R4.1
unnamed: C1.2, J1.2

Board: 2 copper layers, 17 parts (0 on the bottom side), 9 nets, no tracks yet.

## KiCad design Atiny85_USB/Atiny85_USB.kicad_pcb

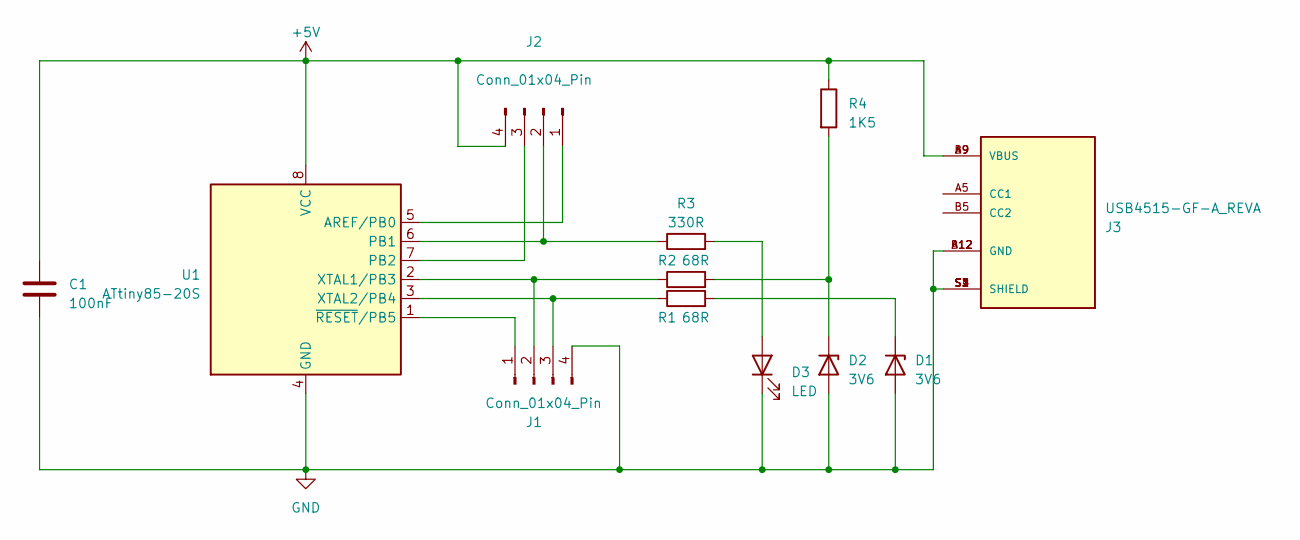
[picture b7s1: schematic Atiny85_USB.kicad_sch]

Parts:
C1: 100nF; C_0805_2012Metric_Pad1.18x1.45mm_HandSolder
D1, D2: 3V6; D_0805_2012Metric_Pad1.15x1.40mm_HandSolder
D3: LED; LED_D3.0mm
J1, J2: Conn_01x04_Pin; PinHeader_1x04_P2.54mm_Vertical
J3: USB4515-GF-A_REVA; GCT_USB4515-GF-A_REVA; PARTREV A
R1, R2: 68R; R_0805_2012Metric_Pad1.20x1.40mm_HandSolder
R3: 330R; R_0805_2012Metric_Pad1.20x1.40mm_HandSolder
R4: 1K5; R_0805_2012Metric_Pad1.20x1.40mm_HandSolder
U1: ATtiny85-20S; SOIC-8W_5.3x5.3mm_P1.27mm

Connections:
+5V: C1.1, J2.4, J3.A9 (VBUS), J3.B9 (VBUS), R4.1, U1.8 (VCC)
GND: C1.2, D1.2 (A), D2.2 (A), D3.1 (K), J1.4, J3.A12 (GND), J3.B12 (GND), J3.S1 (SHIELD), J3.S2 (SHIELD), J3.S3 (SHIELD), J3.S4 (SHIELD), U1.4 (GND)
unnamed: D1.1 (K), R1.2
unnamed: D2.1 (K), R2.2, R4.2
unnamed: D3.2 (A), R3.2
unnamed: J1.1, U1.1 (~RESET/PB5)
unnamed: J1.2, R2.1, U1.2 (XTAL1/PB3)
unnamed: J1.3, R1.1, U1.3 (XTAL2/PB4)
unnamed: J2.1, U1.5 (AREF/PB0)
unnamed: J2.2, R3.1, U1.6 (PB1)
unnamed: J2.3, U1.7 (PB2)

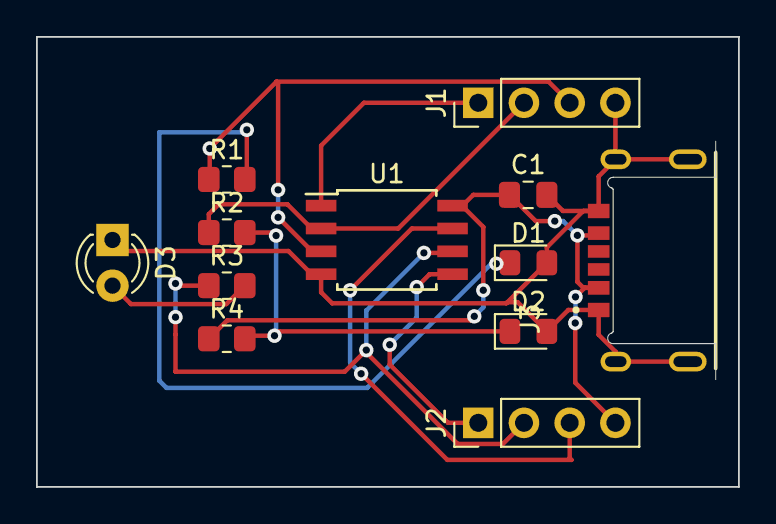
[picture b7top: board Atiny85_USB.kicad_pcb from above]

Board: 2 copper layers, 39.0 x 25.0 mm, 12 parts (0 on the bottom side), 11 nets.

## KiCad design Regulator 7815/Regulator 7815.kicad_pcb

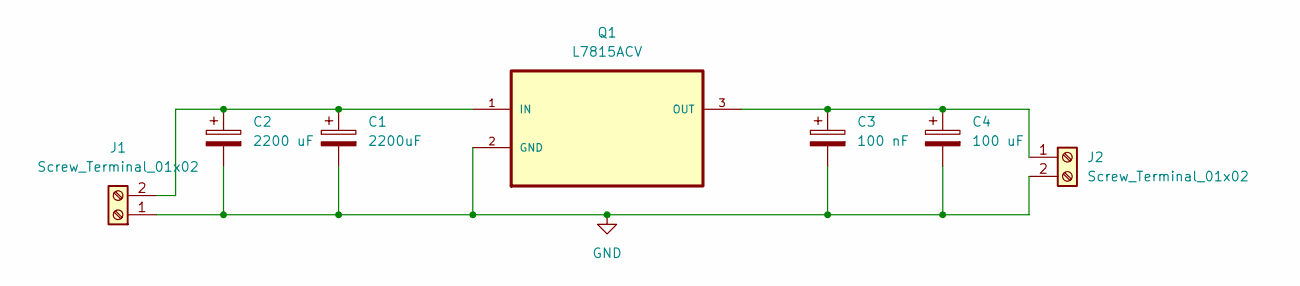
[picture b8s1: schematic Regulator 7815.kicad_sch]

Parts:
C1: 2200uF; CP_Radial_D7.5mm_P2.50mm
C2: 2200 uF; CP_Radial_D7.5mm_P2.50mm
C3: 100 nF; CP_Radial_D4.0mm_P2.00mm
C4: 100 uF; CP_Radial_D7.5mm_P2.50mm
J1, J2: Screw_Terminal_01x02; TerminalBlock_Phoenix_MKDS-1,5-2-5.08_1x02_P5.08mm_Horizont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
Q1: L7815ACV; STM L7815ACV; MPN L7815ACV

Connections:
GND: C1.2, C2.2, C3.2, C4.2, J1.1, J2.2, Q1.2 (GND)
unnamed: C1.1, C2.1, J1.2, Q1.1 (IN)
unnamed: C3.1, C4.1, J2.1, Q1.3 (OUT)

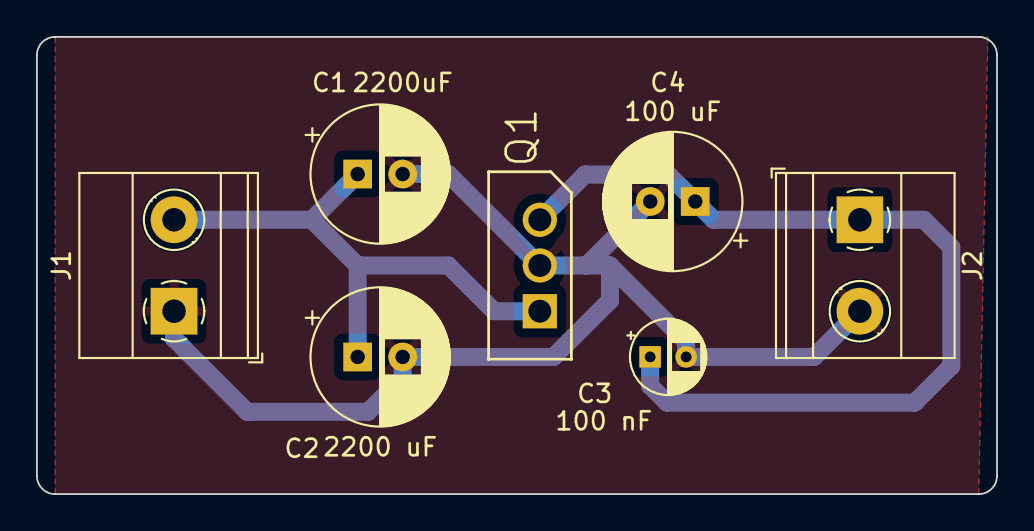
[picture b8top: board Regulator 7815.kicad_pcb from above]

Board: 2 copper layers, 53.3 x 25.4 mm, 7 parts (0 on the bottom side), 3 nets.

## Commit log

2025-02-01 menambahkan projek stm32
